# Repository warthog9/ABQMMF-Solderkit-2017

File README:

This is the learn to solder badge for the Albuquerque Mini Maker Faire.

License:
	The design is opened based on the Creative Commons CC-BY-SA 4.0
	https://creativecommons.org/licenses/by-sa/4.0/

	Copyright on the badge is held by John 'Warthog9' Hawley
	
	Copyright to the outline (shape) of the badge is Dr. Terri Oda

	Copyright of the PCBWay Logo is copyright of PCBWay and is used
	with permission specifically for the run of kits used by
	ABQ MMF in 2017

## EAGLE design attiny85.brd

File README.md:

This is the learn to solder badge for the Albuquerque Mini Maker Faire.

License:
	The design is opened based on the Creative Commons CC-BY-SA 4.0
	[https://creativecommons.org/licenses/by-sa/4.0/](https://creativecommons.org/licenses/by-sa/4.0/)

	Copyright on the badge is held by John 'Warthog9' Hawley
	
	Copyright to the outline (shape) of the badge is Dr. Terri Oda

	Copyright of the PCBWay Logo is copyright of PCBWay and is used
	with permission specifically for the run of kits used by
	ABQ MMF in 2017

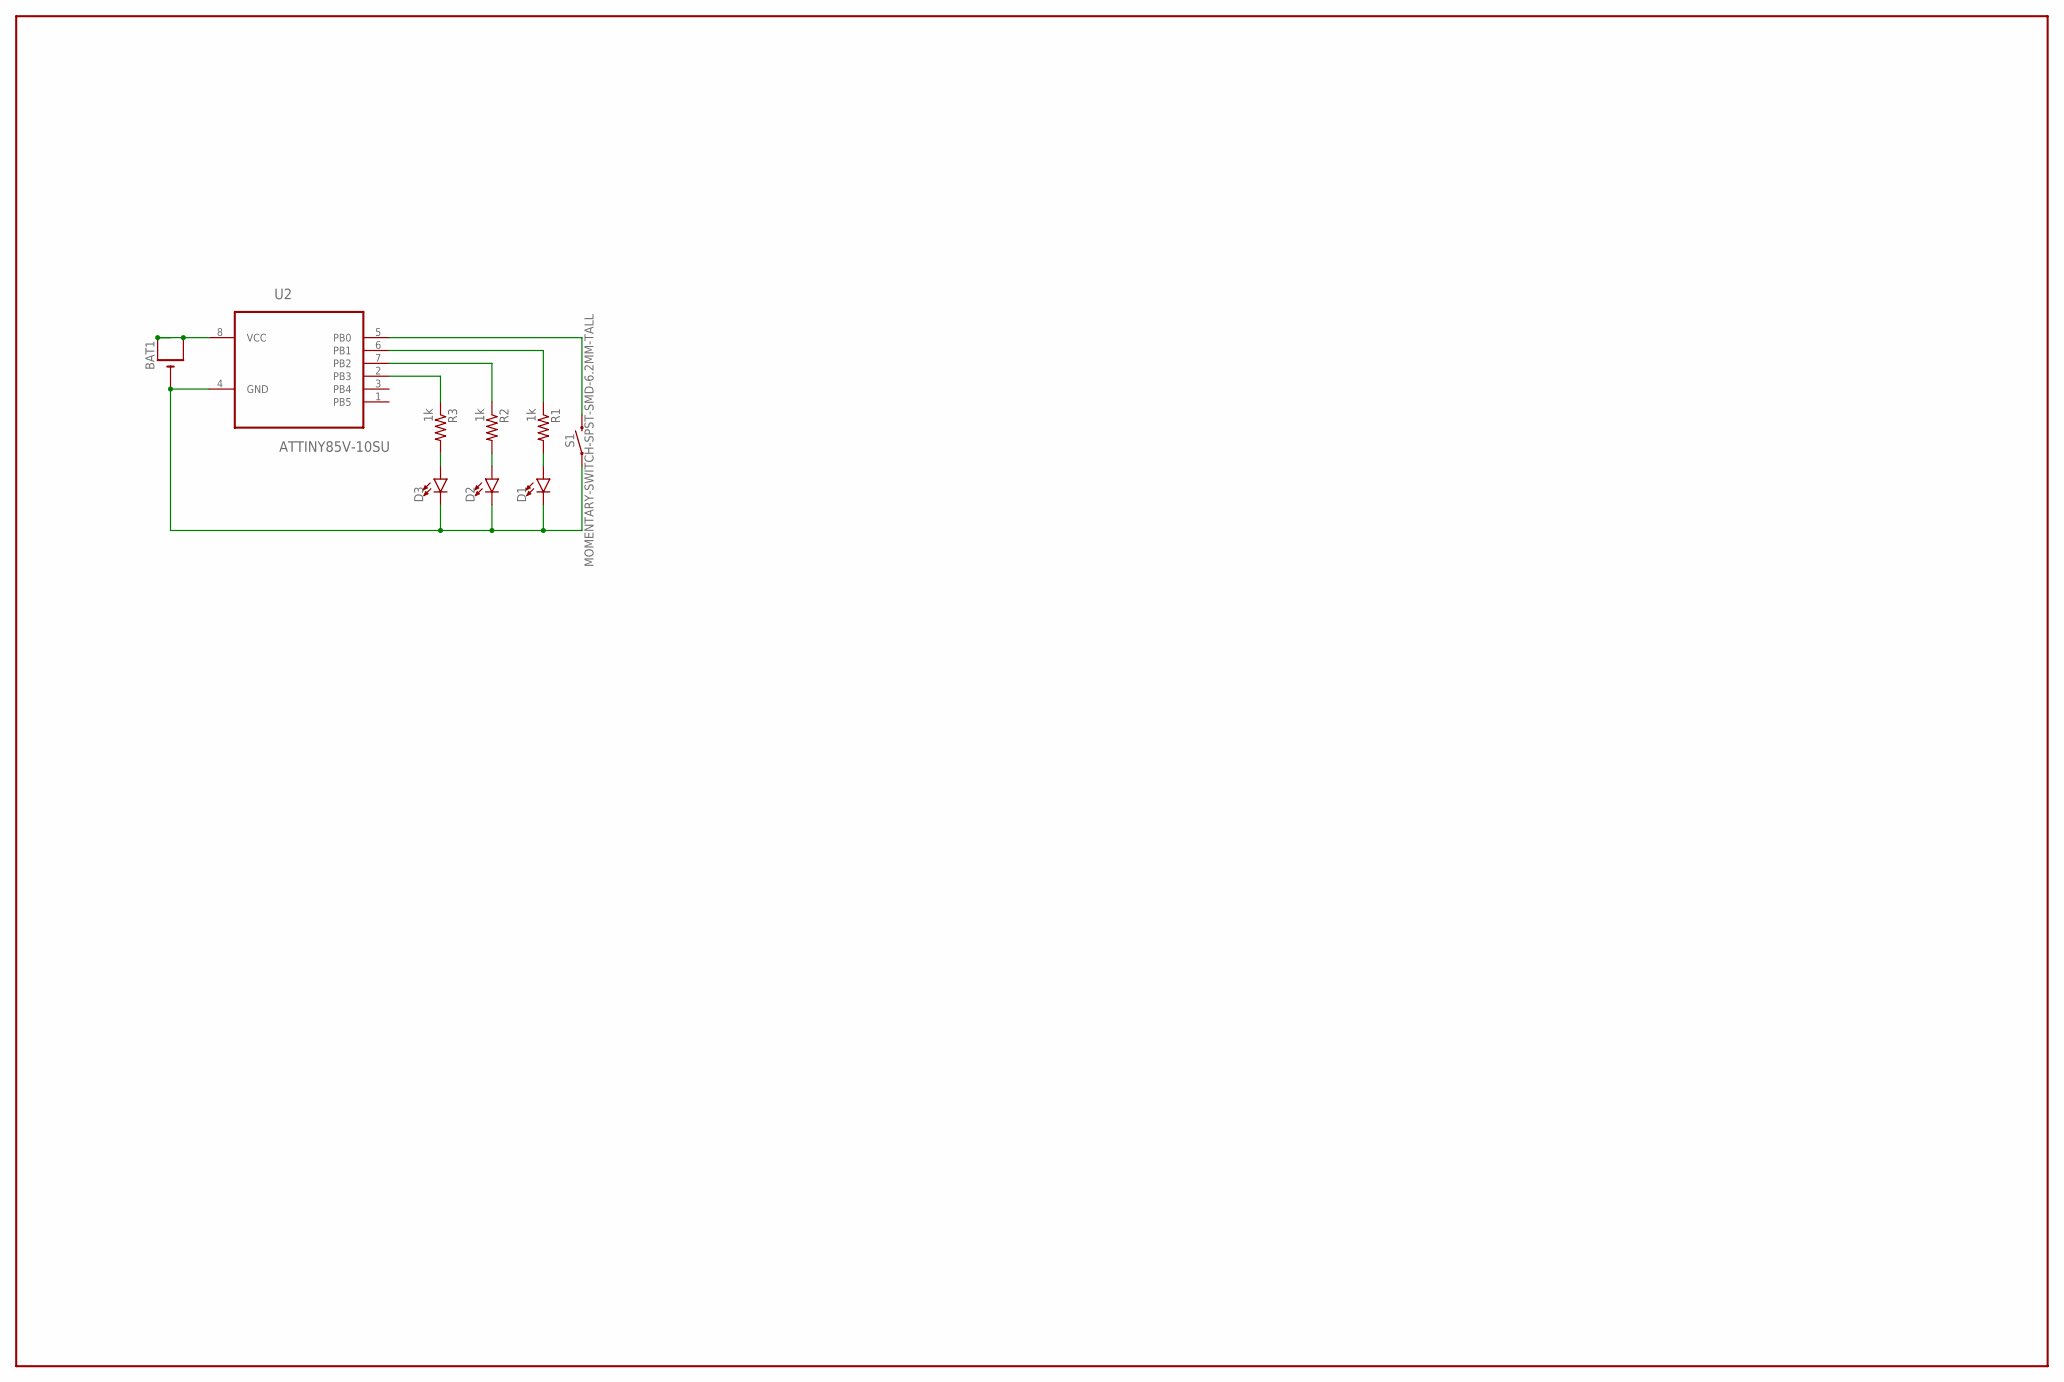
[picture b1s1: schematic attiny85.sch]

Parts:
BAT1: CR2032SMT; CR2032-SMD
D1, D2, D3: LED1206; LED-1206
R1, R2, R3: 1k; M1206
S1: MOMENTARY-SWITCH-SPST-SMD-6.2MM-TALL; TACTILE_SWITCH_SMD_6.2MM_TALL
U2: ATTINY85V-10SU; SOIC127P798X216-8N

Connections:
GND: BAT1.-, D1.C, D2.C, D3.C, S1.A2 (1), U2.4 (GND)
unnamed: D3.A, R3.2
unnamed: D2.A, R2.2
unnamed: S1.B2 (2), U2.5 (PB0)
unnamed: R1.1, U2.6 (PB1)
unnamed: D1.A, R1.2
unnamed: R2.1, U2.7 (PB2)
unnamed: R3.1, U2.2 (PB3)
VCC: BAT1.+$1 (+), BAT1.+$2 (+1), U2.8 (VCC)

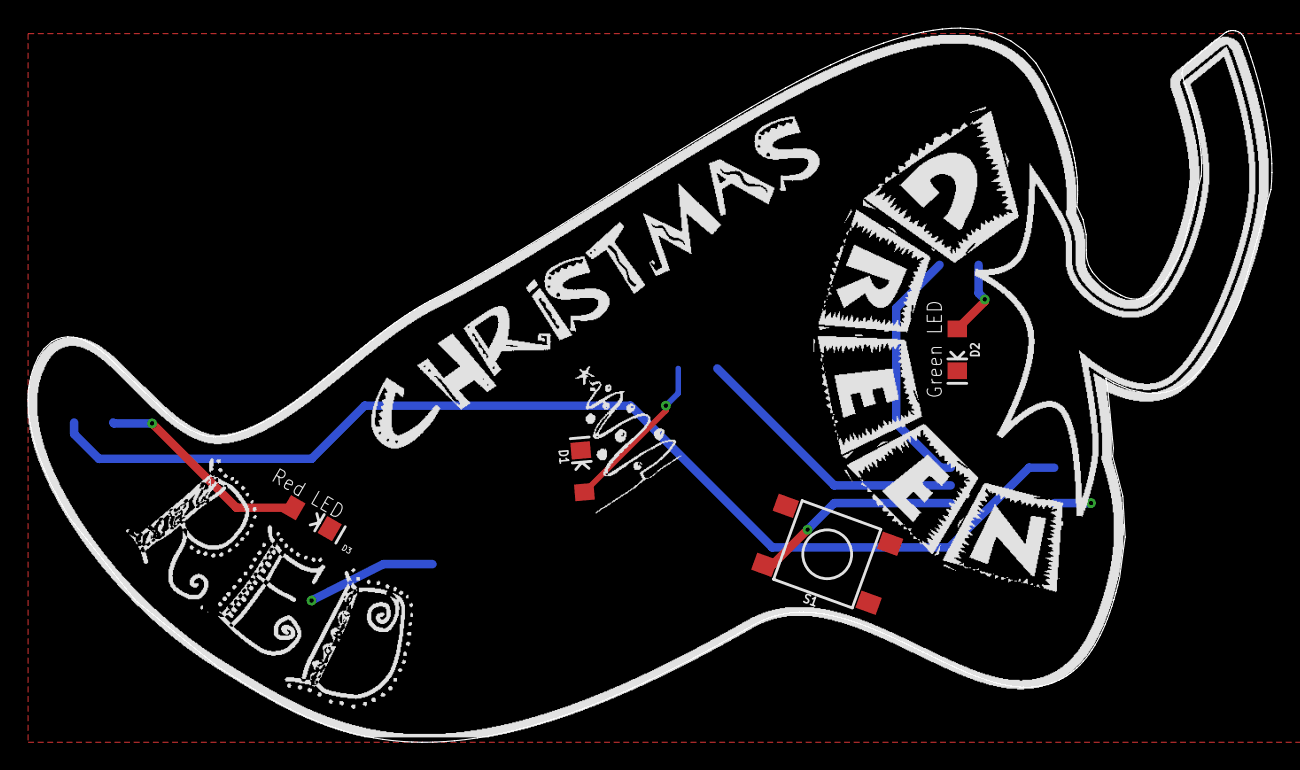
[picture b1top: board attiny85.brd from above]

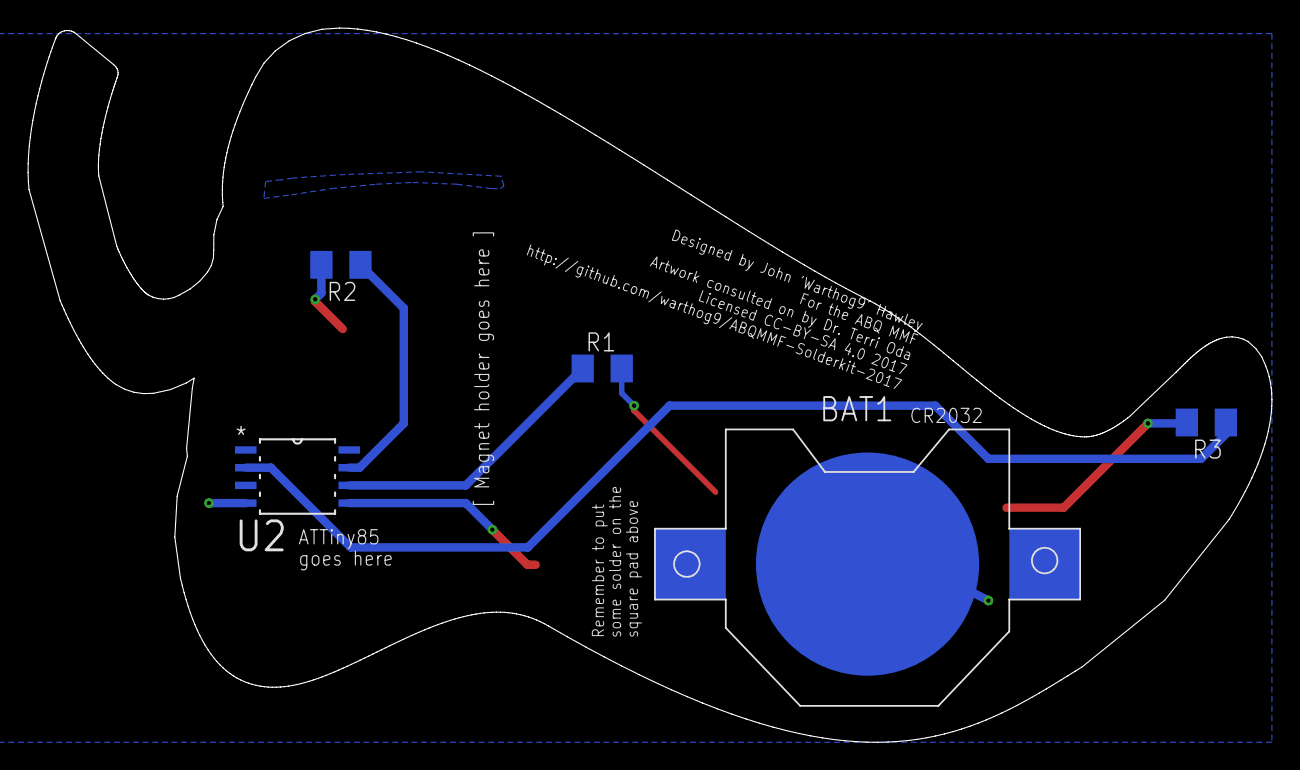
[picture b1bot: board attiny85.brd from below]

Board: 2 copper layers, 89.2 x 51.2 mm, 9 parts (5 on the bottom side), 9 nets.

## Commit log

2016-05-29 Initial Commit w/ README
2016-07-24 Adding .gitignore
2017-01-02 Adding Board Schematic, Layout, & additional files for design
2017-05-29 Removing Balloon specific pieces for Chile conversion
2017-06-16 Initial Artwork commit
2017-06-16 Final artwork
2017-06-16 Updated schematic and layout for surface mount components
2017-06-16 Outline script generated from dxf import
2017-06-16 Updating the README for the latest version
2017-06-16 Minor updates relating to adding the PCBWay Logo
2017-06-16 PCBWay Logo bmp.scr file
2017-06-25 Too many bitmap scripts, delete this one
2017-06-25 Adding in the PCBWay Logos
2017-06-25 More graphics pieces
2017-06-25 Renders for showing
2017-06-25 Adding current gerbers
2017-07-08 Moving R3 to be more accessible
2017-07-08 Moving the notice about the solder dob
2017-07-08 Increase font size of CR2032, and info
2017-07-08 Shrinking the border around the pcbway logo underline
2017-07-10 Flipping to output through the attiny
2017-07-10 Remove extraneous files
2017-07-10 Updating pads and rerouting
2017-07-18 Adding in new outline dxf
2017-07-18 Updating graphics
2017-07-18 Updating the board and schematic
    This is a fairly big set of changes based on the prototype, going
    to run another round just to be sure since I've got enough time.
2017-07-18 Updating gerbers to latest version
2017-07-18 Switching to using the "3" PWMs for the LEDs
2017-07-18 Updating gerbers to latest
2017-08-11 Using a smaller frame on the schematic
2017-08-11 Adding the schematic
2017-08-11 Adding Arduino Source Code + hex output
    This requires that you have the Arduino board information from
    https://github.com/damellis/attiny
    which is more easily consumed from Sparkfun's site here:
    https://cdn.sparkfun.com/assets/learn_tutorials/1/5/0/attiny-ide-1.6.x.zip
    an entire tutorial on how to set this up can be found here:
    https://learn.sparkfun.com/tutorials/tiny-avr-programmer-hookup-guide
2017-08-11 Adding latest gerbers
2017-08-11 Changing up the readme so it's a bit more markdown friendly

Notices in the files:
attiny85.brd:
Licensed CC-BY-SA 4.0 2017
parts and their libraries:
SparkFun-LED: Licensing: Creative Commons ShareAlike 4.0 International - https://creativecommons.org/licenses/by-sa/4.0
